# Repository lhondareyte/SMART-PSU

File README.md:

# SMART PSU for ARM SBC
This is a smart power switch for ARM SBC. This provides a gracefull shutdown and power-off for any tiny board computer that support FreeBSD+libgpio.

This tested OK on 
* Nanopi Neo
* Nanopi Neo Air
* Orange PI
* Raspberry PI B
* Raspberry PI 3

## How it's work?
When plugging in, the board is poweroff and the switch device enter in sleep mode to reduce power consumption.  Just press the switch to power on the board. If you press again the button within 1.5 seconds, the board is poweroff immediatly. 

In normal operation (when operating system is running), the ```psud``` daemon wait for key pressed to perform specified action. The default configuration file is as follow:

```
# psud configuration file
# $Id$  /etc/psud.conf
PSUD_PIN=3                       # My configuration on NanoPI Neo
PSUD_CMD="/sbin/shutdown -p now"	
PSUD_OPT="Dont Care"             # Nothing special
```
In ```/etc/rc.conf```, adds the following line

```
psud_enable="YES"
```
Start ```psud``` 

```
service psud start
```
So, just press button to gracefully shutdown the system. After the configured delay (by dip-switch), the board is powered-off.

## AC Recovery mode
AC Power Recovery
Allows you to set how the system reacts after AC power is restored to the system. By default, the AC Power Recovery option is set to "Power OFF". The other option is "last state".

## Nanobsd configuration
Since all persistents filesystems are mount read-only, there is no need for graceful shutdown with nanobsd. But you probably need to save your configuration on shutdown. You can achieve this with the following script:

```
#!/bin/sh
#
# file: /usr/local/bin/save_configuration.sh
#
mount /cfg || exit 1
find /cfg -type f -print | sed -e '/^\/cfg//' | while read f
do
	if [ -f /etc/$f ] ; then
		cp -p /etc/$f /cfg/$f
	fi
done
sync;sync;sync
umount /cfg
```
Edit ```/etc/psud.conf``` as follows:

```
PSUD_PIN=1                    # Power switch pin, hardware dependent
PSUD_CMD="/usr/local/bin/save_configuration.sh"

PSUD_OPT="WaitAndShot"        # Wait for $PSUD_CMD to complete before
                              # poweroff. GPIO pin is toggle to HIGH 
                              # after $CMD complete . Any other option
                              # is ignored and power off is achieved after
                              # $SHUTDOWN_TIMEOUT
```

## About files
```
 psud/        psud daemon sources
 kicad/       KiCad schematic
 firmware/    source code for AVR attiny13/13a and atmega328p
 refs/        Some MOSFET-P datasheets
```

## LICENSE
Released under the MIT License

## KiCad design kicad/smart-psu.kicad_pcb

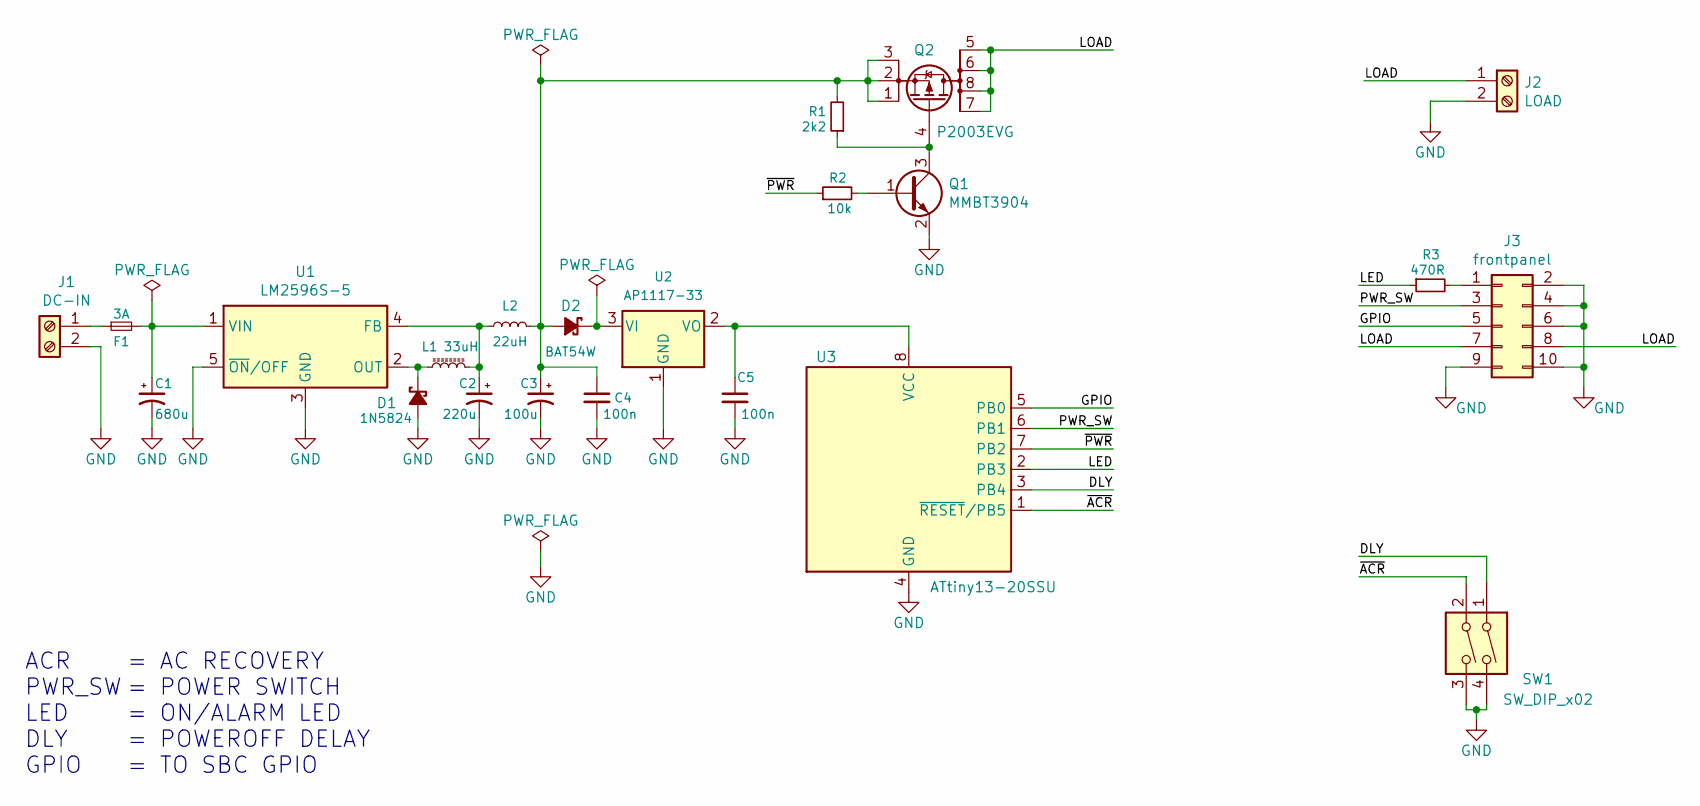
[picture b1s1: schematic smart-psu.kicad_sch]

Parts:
C1: 680u; C_Radial_D10.0mm_H20.0mm_P5.00mm
C2: 220u; CP_Radial_D8.0mm_P2.50mm
C3: 100u; CP_Radial_D5.0mm_P2.50mm
C4, C5: 100n; C_1206_3216Metric_Pad1.33x1.80mm_HandSolder
D1: 1N5824; D_A-405_P12.70mm_Horizontal
D2: BAT54W; D_1206_3216Metric_Pad1.42x1.75mm_HandSolder
F1: 3A; Fuse_1206_3216Metric_Pad1.42x1.75mm_HandSolder
J1: DC-IN; TerminalBlock_MetzConnect_Type055_RT01502HDWU_1x02_P5.00mm_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
J2: LOAD; TerminalBlock_MetzConnect_Type055_RT01502HDWU_1x02_P5.00mm_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
J3: frontpanel; PinHeader_2x05_P2.54mm_Vertical
L1: 33uH; L_Toroid_Vertical_L21.6mm_W11.4mm_P7.62mm_Pulse_KM-3
L2: 22uH; L_Toroid_Vertical_L21.6mm_W11.4mm_P7.62mm_Pulse_KM-3
Q1: MMBT3904; SOT-23
Q2: P2003EVG; SOIC-8_3.9x4.9mm_P1.27mm
R1: 2k2; R_1206_3216Metric_Pad1.30x1.75mm_HandSolder
R2: 10k; R_1206_3216Metric_Pad1.30x1.75mm_HandSolder
R3: 470R; R_1206_3216Metric_Pad1.30x1.75mm_HandSolder
SW1: SW_DIP_x02; SW_DIP_SPSTx02_Slide_9.78x7.26mm_W7.62mm_P2.54mm
U1: LM2596S-5; TO-263-5_TabPin3
U2: AP1117-33; SOT-223-3_TabPin2
U3: ATtiny13-20SSU; SOIC-8_3.9x4.9mm_P1.27mm

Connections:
/DLY: SW1.1, U3.3 (PB4)
/GPIO: J3.5, U3.5 (PB0)
/LED: R3.1, U3.2 (PB3)
/LOAD: J2.1, J3.7, J3.8, Q2.5 (D), Q2.6 (D), Q2.7 (D), Q2.8 (D)
/PWR_SW: J3.3, U3.6 (PB1)
/~ACR: SW1.2, U3.1 (~RESET/PB5)
/~PWR: R2.1, U3.7 (PB2)
GND: C1.2, C2.2, C3.2, C4.2, C5.2, D1.2 (A), J1.2, J2.2, J3.2, J3.4, J3.6, J3.9, J3.10, Q1.2 (E), SW1.3, SW1.4, U1.3 (GND), U1.5 (~ON/OFF), U2.1 (GND), U3.4 (GND)
unnamed: C1.1, F1.2, U1.1 (VIN)
unnamed: C2.1, L1.2, L2.2, U1.4 (FB)
unnamed: C3.1, C4.1, D2.2 (A), L2.1, Q2.1 (S), Q2.2 (S), Q2.3 (S), R1.2
unnamed: C5.1, U2.2 (VO), U3.8 (VCC)
unnamed: D1.1 (K), L1.1, U1.2 (OUT)
unnamed: D2.1 (K), U2.3 (VI)
unnamed: F1.1, J1.1
unnamed: J3.1, R3.2
unnamed: Q1.1 (B), R2.2
unnamed: Q1.3 (C), Q2.4 (G), R1.1

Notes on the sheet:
ACR PWR_SW LED DLY GPIO
= AC RECOVERY = POWER SWITCH = ON/ALARM LED = POWEROFF DELAY = TO SBC GPIO

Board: 2 copper layers, 22 parts (0 on the bottom side), 18 nets, no tracks yet.

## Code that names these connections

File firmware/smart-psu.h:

/*
 * Copyright (c) 2018-2021 Luc Hondareyte
 *
 * Permission is hereby granted, free of charge, to any person obtaining a copy
 * of this software and associated documentation files (the "Software"), to deal
 * in the Software without restriction, including without limitation the rights
 * to use, copy, modify, merge, publish, distribute, sublicense, and/or sell
 * copies of the Software, and to permit persons to whom the Software is
 * furnished to do so, subject to the following conditions:
 * 
 * The above copyright notice and this permission notice shall be included in all
 * copies or substantial portions of the Software.
 *
 * THE SOFTWARE IS PROVIDED "AS IS", WITHOUT WARRANTY OF ANY KIND, EXPRESS OR
 * IMPLIED, INCLUDING BUT NOT LIMITED TO THE WARRANTIES OF MERCHANTABILITY,
 * FITNESS FOR A PARTICULAR PURPOSE AND NONINFRINGEMENT. IN NO EVENT SHALL THE
 * AUTHORS OR COPYRIGHT HOLDERS BE LIABLE FOR ANY CLAIM, DAMAGES OR OTHER
 * LIABILITY, WHETHER IN AN ACTION OF CONTRACT, TORT OR OTHERWISE, ARISING FROM,
 * OUT OF OR IN CONNECTION WITH THE SOFTWARE OR THE USE OR OTHER DEALINGS IN THE
 * SOFTWARE.
 */
 
#ifndef __POWER_BUTTON_H__
 #define __POWER_BUTTON_H__

#define F_CPU		4800000UL

#include <avr/eeprom.h>
#include <avr/interrupt.h>
#include <avr/io.h>
#include <avr/pgmspace.h>
#include <avr/power.h>
#include <avr/sleep.h>
#include <stdlib.h>
#include <stdint.h>
#include <util/delay.h>

/*
 * Hardware Configuration
 */

#if defined (__AVR_ATtiny13A__)  || defined (__AVR_ATtiny13__)

#undef F_CPU
#define F_CPU		4800000UL
#define INTMSKR		GIMSK		// Interupt mask register
#define INTRGST		MCUCR		// Interrupt register

#define D_PORT		DDRB
#define O_PORT		PORTB
#define I_PORT		PINB
#define GPIO		0
#define PWR_SW		1
#define PWR		2
#define FAULT		3
#define DELAY		4
#define ACR		5
#define LED_MASK	4
#define FAULT_MASK	8
#define TICKS		16

#elif defined (__AVR_ATmega328P__)

#undef F_CPU
#define F_CPU		16000000UL
#define INTMSKR		EIMSK		// Interupt mask register
#define INTRGST		EICRA		// Interrupt register 

#define D_PORT		DDRD
#define O_PORT		PORTD
#define I_PORT		PIND
#define PWR_SW		2
#define GPIO		3
#define PWR		4
#define DELAY		5
#define FAULT		6
#define ACR		7
#define LED_MASK	4
#define FAULT_MASK	8
#define TICKS		66

#else
 #error "Device not supported"
#endif

/*
 * Macros
 */
#define STATUS		1

#define loadConfiguration()	 eeprom_read_byte((uint8_t *)STATUS)
#define saveConfiguration(n)	 eeprom_write_byte((uint8_t *)STATUS,n)

#define setBit(octet,bit)     ( octet |= (1<<bit))
#define clearBit(octet,bit)   ( octet &= ~(1<<bit))
#define toggleBit(octet,bit)  ( octet ^= (1<<bit))
#define enable_INT0()         setBit(INTMSKR,INT0)
#define disable_INT0()        clearBit(INTMSKR,INT0)

#if defined (__BREADBOARD__)
  #define switchOn()	setBit(O_PORT,PWR)
  #define switchOff(n)	clearBit(O_PORT,PWR)
#else
  #define switchOn()	clearBit(O_PORT,PWR)
  #define switchOff()	setBit(O_PORT,PWR)
#endif

/*
 * Misc
 */
#define NO			0
#define YES			1
#define OFF			0
#define ON			1
#define SHUTDOWN_TIMEOUT	5000    // Time to wait before force power off (ms)
#define STARTUP_TIMEOUT		1500    // Time before startup that we can force poweroff (ms)

uint16_t volatile ms_seconds;
uint8_t volatile ticks;

/*
 * Prototypes
 */
void blink(uint8_t, uint8_t);
void setupHardware(void);
void store(void);
void shutdown(void);
void ms_wait(uint8_t);
void startTimer(uint16_t);
void stopTimer(void);
void PowerOff(void);

#define alarm(n) blink(FAULT,n)

#endif /* __POWER_BUTTON_H__ */

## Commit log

2018-01-09 Adding kicad files
2018-01-09 Adding firmware: basic on/off
2018-01-09 Update makefile
2018-02-02 Disable INT0 while switch is not released.
2018-02-03 Adding new layout in schematic.
2018-02-06 Set footprint for all components.
2018-03-24 Change pinout according to new design
2018-03-25 Adding buttond.c : POC Ok
2018-03-25 Compile OK with gmake. Configuration file's parser works.
2018-03-25 Rename project to smart-psu+psud
2018-03-25 Minors change on keywords
2018-03-25 Adding psud startup for FreeBSD
2018-03-25 Rename firmware files
2018-03-25 Configure INT0 pour attiny13x
2018-03-25 Move some defines to header file
2018-03-25 Now works on attiny13
2018-03-25 Power switch on INT0
2018-03-25 Adding special targets for atmega168
2018-03-25 Adding reload option
2018-03-26 Indentation style uniformization
2018-03-29 execl command Ok
2018-03-29 Adding license.
2018-03-31 make/gmake compatibility
2018-03-31 More controls about daemon's state
2018-04-01 Remove double commas from token
2018-04-01 Adding signal handling and lock
2018-04-01 Adding sample config file
2018-04-03 Daemonize psud.
2018-04-05 Initialize struct config before use.
2018-04-11 Wait for child process before continue. Adding psud_opt WaitAndShoot.
2018-04-11 Adding syslog support.
2018-04-22 Avoid double exec + indentation
2018-04-22 New indentation
2018-04-24 Minors changes
2018-04-24 Syslogd needed.
2018-04-28 Rename to psud.conf
2018-04-28 Reload configuration on SIGHUP.
2018-05-03 Clear configuration before reload.
2018-05-10 Padding binary file to 1k (minipro do not erase cpu)
2018-05-10 Add conditionnal padding.
2018-05-26 Update schematic for high-side switch.
2018-06-22 Adding some P-channel MOSFET datasheets.
2018-08-03 Upgrade to Kicad 5.0
2018-10-06 Adding AC recovery configuration pin.
2018-10-28 Update Makefile.
2019-03-10 move memset() to parser.
2019-03-10 Accidentaly delete rescue-lib
2020-01-09 Rename parser.c
2020-01-09 Small change
2020-01-13 Single Makefile
2021-01-26 Fix segfault on config parse. get_config() return an error if some vars are missing.
2021-03-29 Rewrite delete_doubleCommas to removeDoubleCommas() and call once
2021-03-29 move memset to get_config. Add SIGHUP signal. rename psu_config struct to config.
2021-03-29 Code simplification
2021-03-31 firmware : remove gmake dependencie
2021-03-31 firmware : almost works on breadboard.
2021-03-31 Update schematic
2021-04-01 Add fault on quick power off.
2021-04-01 Update Makefile to create fuses.txt for attiny13
2021-04-01 Works on attiny13
2021-04-01 Add README.md
2021-04-02 CONFILE is not known in get_config.
2021-04-03 Import untested AC recovery mode
2021-06-28 Fix compilation with clang 11.0
2021-10-20 Adding LICENSE file
2021-10-21 Updating License in source files
2021-11-06 Waiting for PSU stabilization and fix compilation with avr-gcc 10.2 (need more fixs)
2021-11-06 Update frontpanel connector
2021-11-06 One uniq file
2021-11-06 Remove -fcommon compilation option
2022-01-07 Fix psud.h dependency in config.*
2023-02-12 Update to KiCad 6
2024-05-16 Use DESTDIR and PREFIX variables
